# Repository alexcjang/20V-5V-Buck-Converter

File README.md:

# 20V-5V Buck Converter

## Overview
Goal: fully functioning buck converter that can step down voltage from 20V to 5V with less than 5% ripple. Custom PCB designed with KiCad, assembled with capacitors, inductors, gate driver, MOSFETs, and Op-Amp.

## Key Results
- Peak efficiency: ~85% driving 5W load
- Output ripple: <40mV

## Design
- **Topology:** Asynchronous Buck
- **Duty Cycle:** 0.25 to step down voltage by x4
- **PCB:** 2-layer, component selection to trade off between size and efficiency

## What I'd Change
This was my first real power converter design, which helped me practice circuit design, component selection, and understanding power converters. If I could redo this project, I would definitely use a 4 layer board to optimize my layout a lot and cut down on parasitics from excess loop length. I would also simulate my system first in PLECS or SPICE adjacent software to gain a better understanding of what specs I am targeting and how to achieve them.

## Media

## Tools
LTSpice, KiCAD, Oscilloscope

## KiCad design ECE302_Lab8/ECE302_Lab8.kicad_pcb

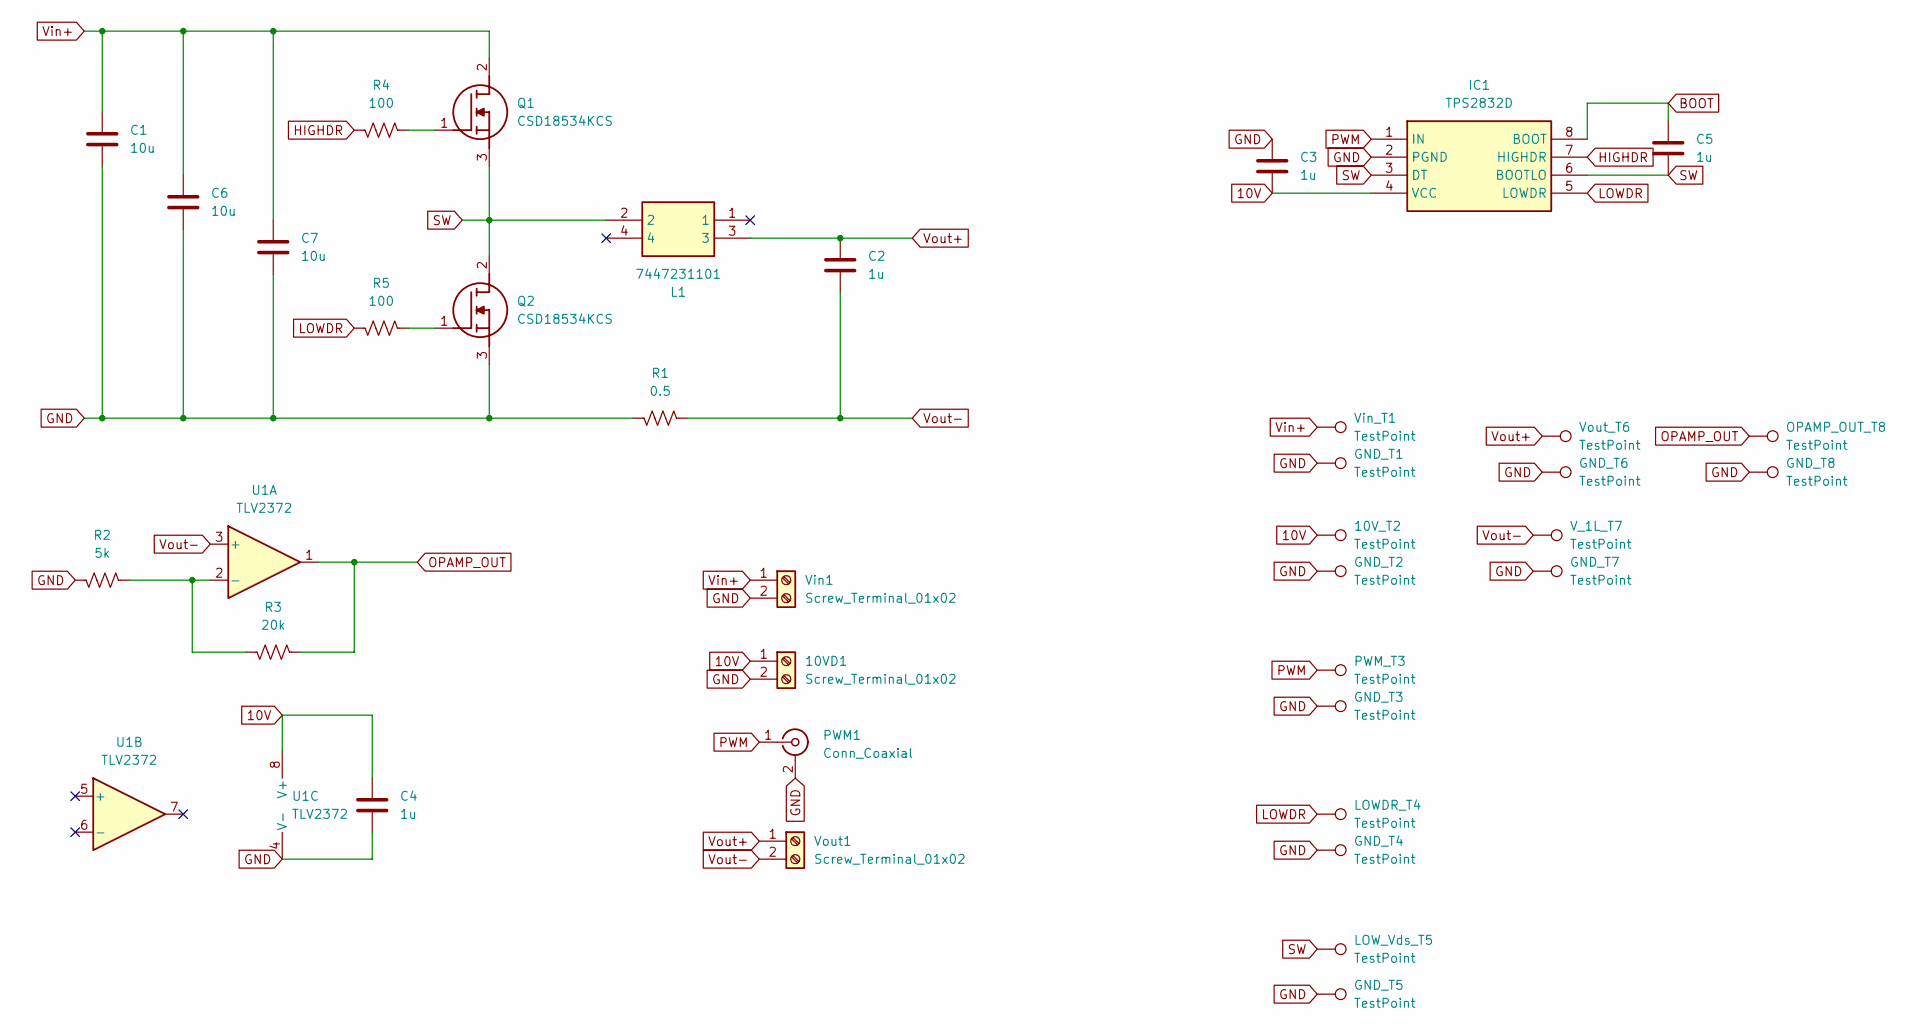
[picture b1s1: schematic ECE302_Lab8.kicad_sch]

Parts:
10VD1: Screw_Terminal_01x02; PhoenixContact_MSTBA_2,5_2-G_1x02_P5.00mm_Horizontal
10V_T2: TestPoint; TestPoint_Keystone_5010-5014_Multipurpose
C1, C6, C7: 10u; C_Disc_D3.8mm_W2.6mm_P2.50mm
C2, C3, C4, C5: 1u; C_Disc_D3.8mm_W2.6mm_P2.50mm
GND_T1, GND_T2, GND_T3, GND_T4, GND_T5, GND_T6, GND_T7, GND_T8: TestPoint; TestPoint_Keystone_5010-5014_Multipurpose
IC1: TPS2832D; SO-8_3.9x4.9mm_P1.27mm; Manufacturer_Part_Number TPS2832D; Mouser Part Number 595-TPS2832D
L1: 7447231101; Manufacturer_Part_Number 7447231101
LOWDR_T4: TestPoint; TestPoint_Keystone_5010-5014_Multipurpose
LOW_Vds_T5: TestPoint; TestPoint_Keystone_5010-5014_Multipurpose
OPAMP_OUT_T8: TestPoint; TestPoint_Keystone_5010-5014_Multipurpose
PWM1: Conn_Coaxial; BNC_Amphenol_B6252HB-NPP3G-50_Horizontal
PWM_T3: TestPoint; TestPoint_Keystone_5010-5014_Multipurpose
Q1, Q2: CSD18534KCS; TO-220-3_Vertical; Manufacturer_Part_Number CSD18534KCS; Mouser Part Number 595-CSD18534KCS
R1: 0.5; R_Axial_DIN0922_L20.0mm_D9.0mm_P30.48mm_Horizontal
R2: 5k; R_Axial_DIN0207_L6.3mm_D2.5mm_P10.16mm_Horizontal
R3: 20k; R_Axial_DIN0207_L6.3mm_D2.5mm_P10.16mm_Horizontal
R4, R5: 100; R_Axial_DIN0207_L6.3mm_D2.5mm_P10.16mm_Horizontal
U1: TLV2372; SO-8_3.9x4.9mm_P1.27mm
V_1L_T7: TestPoint; TestPoint_Keystone_5010-5014_Multipurpose
Vin1: Screw_Terminal_01x02; PhoenixContact_MSTBA_2,5_2-G_1x02_P5.00mm_Horizontal
Vin_T1: TestPoint; TestPoint_Keystone_5010-5014_Multipurpose
Vout1: Screw_Terminal_01x02; PhoenixContact_MSTBA_2,5_2-G_1x02_P5.00mm_Horizontal
Vout_T6: TestPoint; TestPoint_Keystone_5010-5014_Multipurpose

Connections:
10V: 10VD1.1, 10V_T2.1, C3.2, C4.1, IC1.4 (VCC), U1.8 (V+)
BOOT: C5.1, IC1.8 (BOOT)
GND: 10VD1.2, C1.2, C3.1, C4.2, C6.2, C7.2, GND_T1.1, GND_T2.1, GND_T3.1, GND_T4.1, GND_T5.1, GND_T6.1, GND_T7.1, GND_T8.1, IC1.2 (PGND), PWM1.2 (Ext), Q2.3 (S), R1.1, R2.1, U1.4 (V-), Vin1.2
HIGHDR: IC1.7 (HIGHDR), R4.1
LOWDR: IC1.5 (LOWDR), LOWDR_T4.1, R5.1
unnamed: Q1.1 (G), R4.2
unnamed: Q2.1 (G), R5.2
unnamed: R2.2, R3.1, U1.2 (-)
OPAMP_OUT: OPAMP_OUT_T8.1, R3.2, U1.1
PWM: IC1.1 (IN), PWM1.1 (In), PWM_T3.1
SW: C5.2, IC1.3 (DT), IC1.6 (BOOTLO), L1.2, LOW_Vds_T5.1, Q1.3 (S), Q2.2 (D)
Vin+: C1.1, C6.1, C7.1, Q1.2 (D), Vin1.1, Vin_T1.1
Vout+: C2.1, L1.3, Vout1.1, Vout_T6.1
Vout-: C2.2, R1.2, U1.3 (+), V_1L_T7.1, Vout1.2

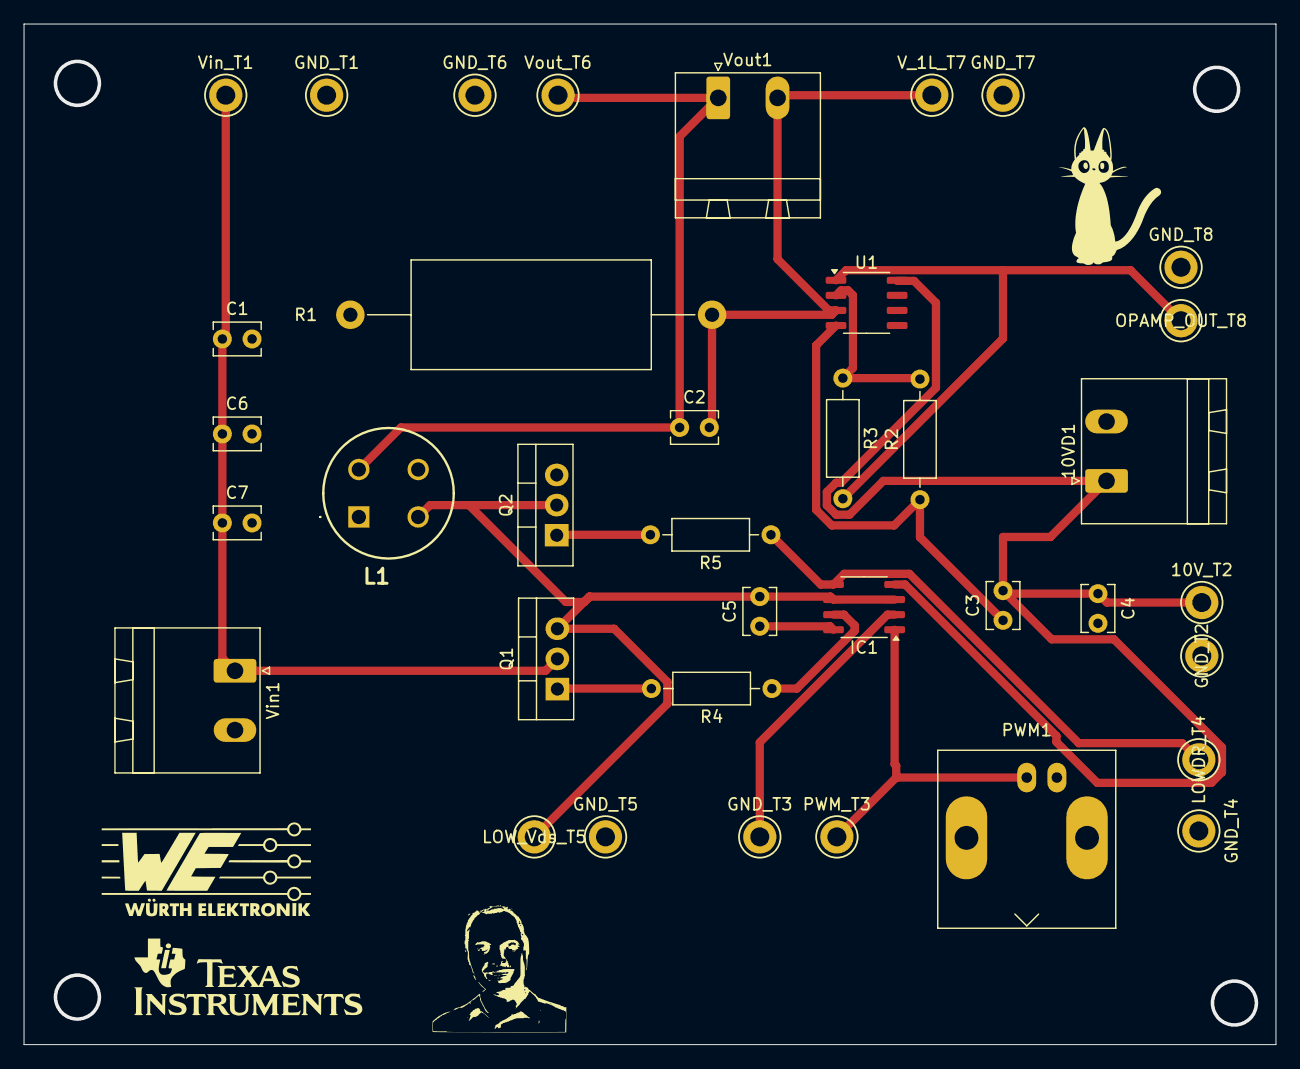
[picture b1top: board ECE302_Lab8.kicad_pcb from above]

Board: 2 copper layers, 105.5 x 86.0 mm, 37 parts (0 on the bottom side), 14 nets.
